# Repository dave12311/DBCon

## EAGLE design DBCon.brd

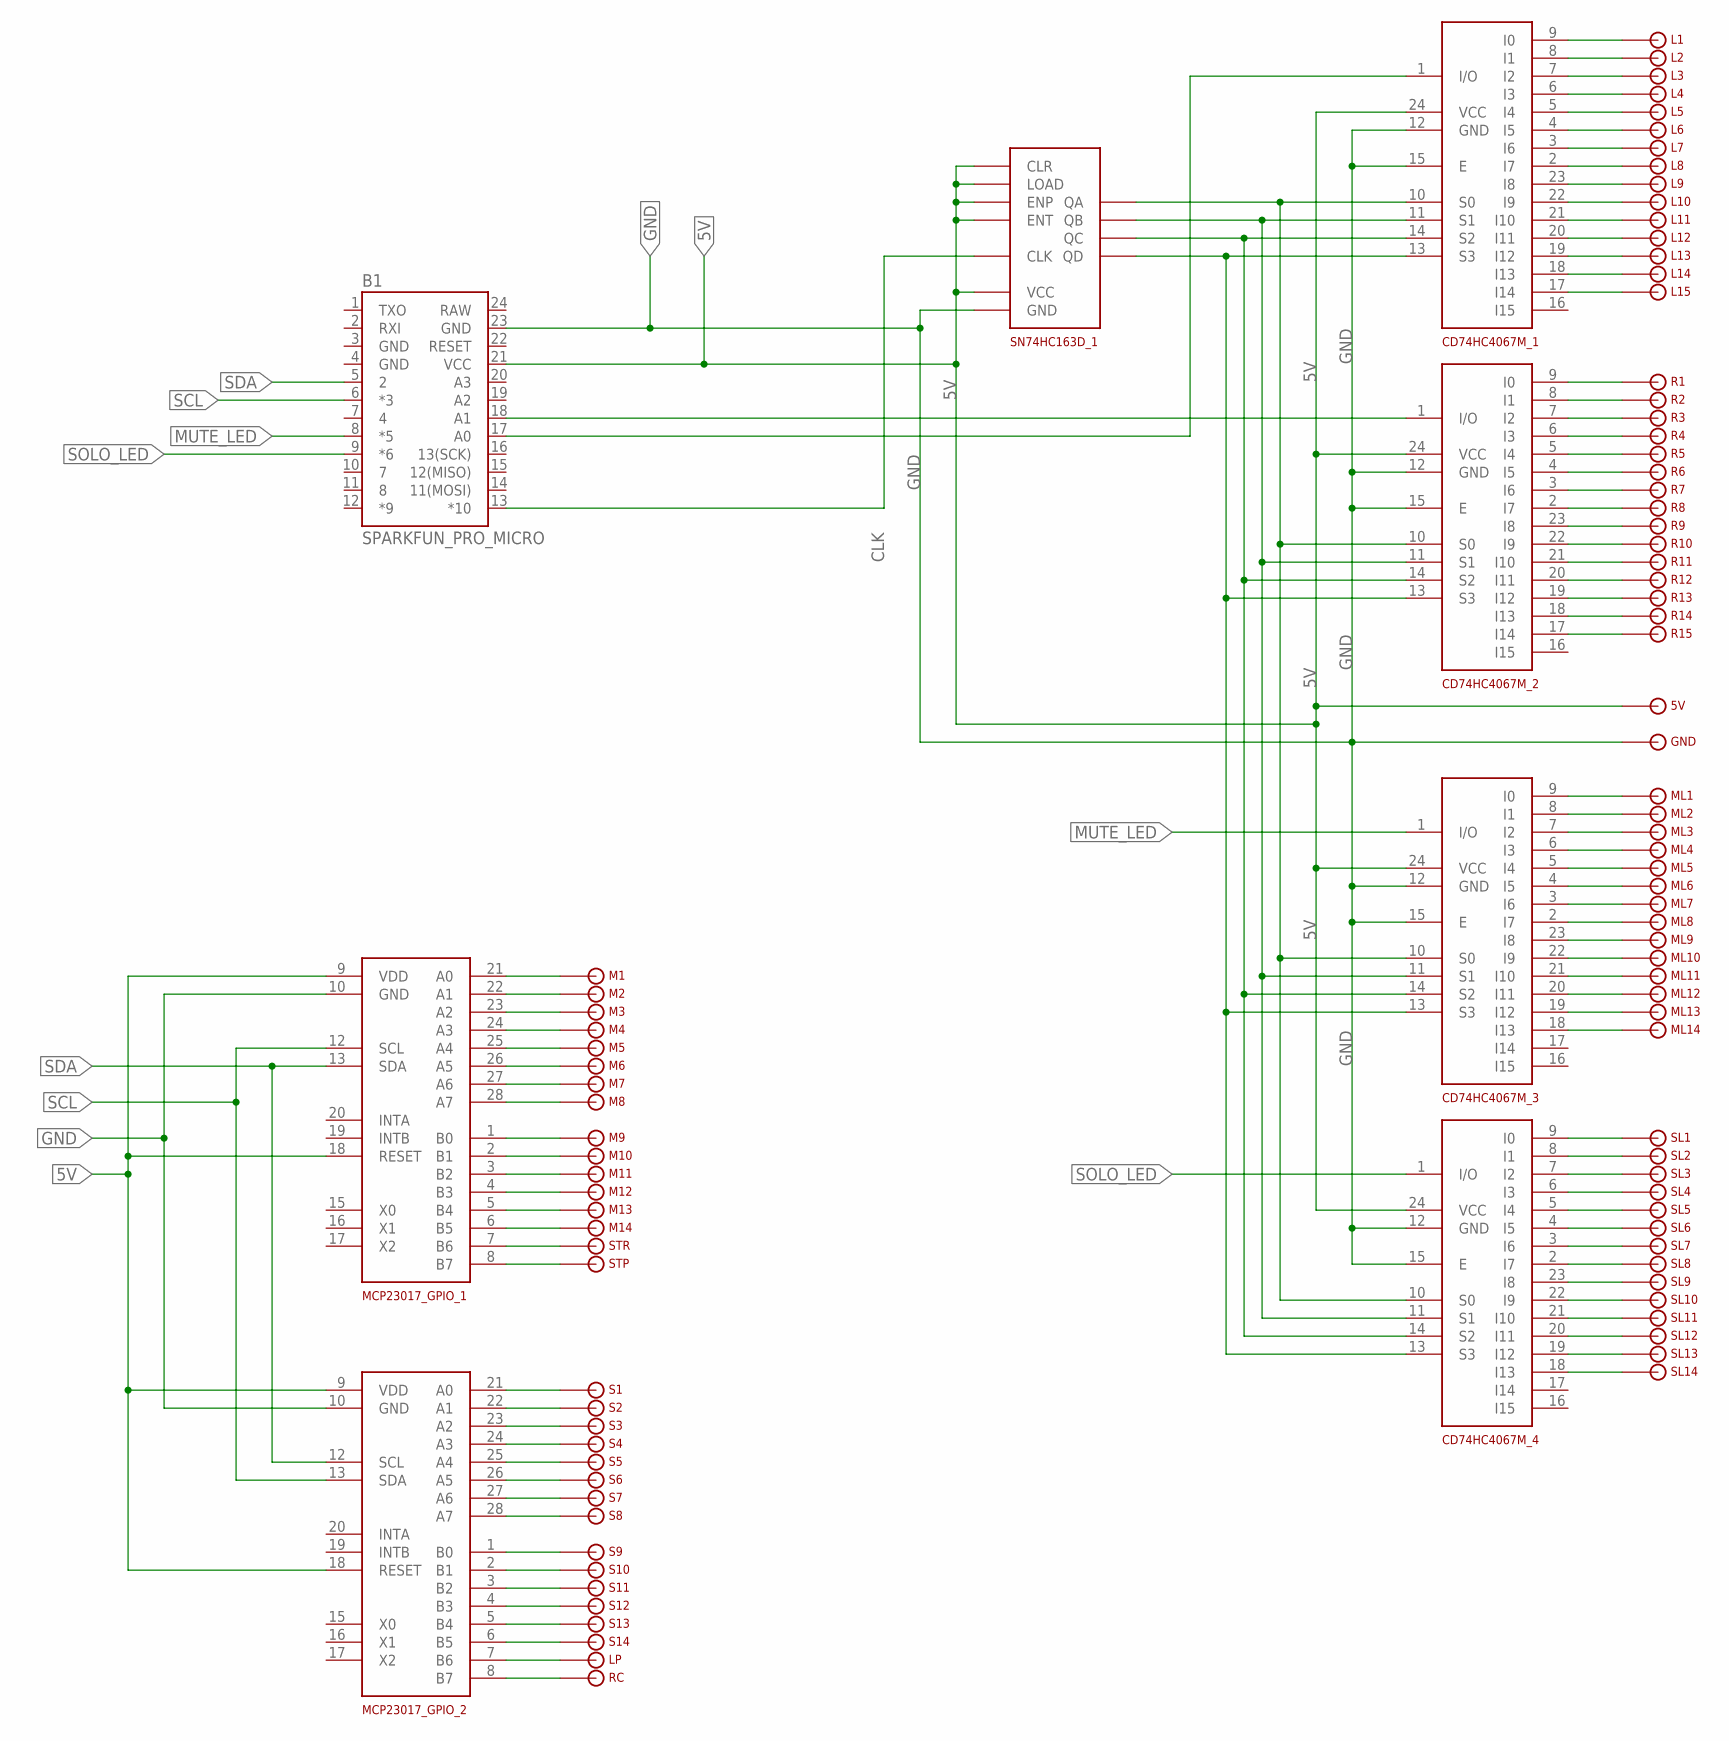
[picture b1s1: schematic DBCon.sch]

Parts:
5V: 1_PIN; CON1
B1: SPARKFUN_PRO_MICRO
CD74HC4067M_1, CD74HC4067M_2, CD74HC4067M_3, CD74HC4067M_4: CD74HC4067M_DEMUX; SO24
GND: 1_PIN; CON1
L1, L2, L3, L4, L5, L6, L7, L8, L9, L10, L11, L12, L13, L14, L15: 1_PIN; CON1
LP: 1_PIN; CON1
M1, M2, M3, M4, M5, M6, M7, M8, M9, M10, M11, M12, M13, M14: 1_PIN; CON1
MCP23017_GPIO_1, MCP23017_GPIO_2: MCP23017_GPIO; DIL28-3
ML1, ML2, ML3, ML4, ML5, ML6, ML7, ML8, ML9, ML10, ML11, ML12, ML13, ML14: 1_PIN; CON1
R1, R2, R3, R4, R5, R6, R7, R8, R9, R10, R11, R12, R13, R14, R15: 1_PIN; CON1
RC: 1_PIN; CON1
S1, S2, S3, S4, S5, S6, S7, S8, S9, S10, S11, S12, S13, S14: 1_PIN; CON1
SL1, SL2, SL3, SL4, SL5, SL6, SL7, SL8, SL9, SL10, SL11, SL12, SL13, SL14: 1_PIN; CON1
SN74HC163D_1: SN74HC163D_COUNTER; SO16
STP: 1_PIN; CON1
STR: 1_PIN; CON1

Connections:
5V: 5V.P$1, B1.21 (VCC), CD74HC4067M_1.24 (VCC), CD74HC4067M_2.24 (VCC), CD74HC4067M_3.24 (VCC), CD74HC4067M_4.24 (VCC), MCP23017_GPIO_1.9 (VDD), MCP23017_GPIO_1.18 (RESET), MCP23017_GPIO_2.9 (VDD), MCP23017_GPIO_2.18 (RESET), SN74HC163D_1.1 (CLR), SN74HC163D_1.7 (ENP), SN74HC163D_1.9 (LOAD), SN74HC163D_1.10 (ENT), SN74HC163D_1.16 (VCC)
A: CD74HC4067M_1.10 (S0), CD74HC4067M_2.10 (S0), CD74HC4067M_3.10 (S0), CD74HC4067M_4.10 (S0), SN74HC163D_1.14 (QA)
B: CD74HC4067M_1.11 (S1), CD74HC4067M_2.11 (S1), CD74HC4067M_3.11 (S1), CD74HC4067M_4.11 (S1), SN74HC163D_1.13 (QB)
C: CD74HC4067M_1.14 (S2), CD74HC4067M_2.14 (S2), CD74HC4067M_3.14 (S2), CD74HC4067M_4.14 (S2), SN74HC163D_1.12 (QC)
CLK: B1.13 (*10), SN74HC163D_1.2 (CLK)
D: CD74HC4067M_1.13 (S3), CD74HC4067M_2.13 (S3), CD74HC4067M_3.13 (S3), CD74HC4067M_4.13 (S3), SN74HC163D_1.11 (QD)
GND: B1.3 (GND), B1.4 (GND), B1.23 (GND), CD74HC4067M_1.12 (GND), CD74HC4067M_1.15 (E), CD74HC4067M_2.12 (GND), CD74HC4067M_2.15 (E), CD74HC4067M_3.12 (GND), CD74HC4067M_3.15 (E), CD74HC4067M_4.12 (GND), CD74HC4067M_4.15 (E), GND.P$1, MCP23017_GPIO_1.10 (GND), MCP23017_GPIO_2.10 (GND), SN74HC163D_1.8 (GND)
L_IO: B1.17 (A0), CD74HC4067M_1.1 (I/O)
MUTE_LED: B1.8 (*5), CD74HC4067M_3.1 (I/O)
unnamed: M1.P$1, MCP23017_GPIO_1.21 (A0)
unnamed: M2.P$1, MCP23017_GPIO_1.22 (A1)
unnamed: M3.P$1, MCP23017_GPIO_1.23 (A2)
unnamed: CD74HC4067M_3.9 (I0), ML1.P$1
unnamed: CD74HC4067M_3.8 (I1), ML2.P$1
unnamed: CD74HC4067M_3.7 (I2), ML3.P$1
unnamed: CD74HC4067M_3.6 (I3), ML4.P$1
unnamed: M4.P$1, MCP23017_GPIO_1.24 (A3)
unnamed: M5.P$1, MCP23017_GPIO_1.25 (A4)
unnamed: CD74HC4067M_1.9 (I0), L1.P$1
unnamed: CD74HC4067M_1.8 (I1), L2.P$1
unnamed: CD74HC4067M_1.7 (I2), L3.P$1
unnamed: CD74HC4067M_1.6 (I3), L4.P$1
unnamed: CD74HC4067M_1.5 (I4), L5.P$1
unnamed: CD74HC4067M_1.4 (I5), L6.P$1
unnamed: CD74HC4067M_1.3 (I6), L7.P$1
unnamed: CD74HC4067M_1.2 (I7), L8.P$1
unnamed: CD74HC4067M_1.23 (I8), L9.P$1
unnamed: CD74HC4067M_1.22 (I9), L10.P$1
unnamed: CD74HC4067M_1.21 (I10), L11.P$1
unnamed: CD74HC4067M_1.20 (I11), L12.P$1
unnamed: CD74HC4067M_1.19 (I12), L13.P$1
unnamed: CD74HC4067M_1.18 (I13), L14.P$1
unnamed: CD74HC4067M_1.17 (I14), L15.P$1
unnamed: CD74HC4067M_2.9 (I0), R1.P$1
unnamed: CD74HC4067M_2.8 (I1), R2.P$1
unnamed: CD74HC4067M_2.7 (I2), R3.P$1
unnamed: CD74HC4067M_2.6 (I3), R4.P$1
unnamed: CD74HC4067M_2.5 (I4), R5.P$1
unnamed: CD74HC4067M_2.4 (I5), R6.P$1
unnamed: CD74HC4067M_2.3 (I6), R7.P$1
unnamed: CD74HC4067M_2.2 (I7), R8.P$1
unnamed: CD74HC4067M_2.23 (I8), R9.P$1
unnamed: CD74HC4067M_2.22 (I9), R10.P$1
unnamed: CD74HC4067M_2.21 (I10), R11.P$1
unnamed: CD74HC4067M_2.20 (I11), R12.P$1
unnamed: CD74HC4067M_2.19 (I12), R13.P$1
unnamed: CD74HC4067M_2.18 (I13), R14.P$1
unnamed: CD74HC4067M_2.17 (I14), R15.P$1
unnamed: M6.P$1, MCP23017_GPIO_1.26 (A5)
unnamed: M7.P$1, MCP23017_GPIO_1.27 (A6)
unnamed: M8.P$1, MCP23017_GPIO_1.28 (A7)
unnamed: M9.P$1, MCP23017_GPIO_1.1 (B0)
unnamed: M10.P$1, MCP23017_GPIO_1.2 (B1)
unnamed: M11.P$1, MCP23017_GPIO_1.3 (B2)
unnamed: M12.P$1, MCP23017_GPIO_1.4 (B3)
unnamed: M13.P$1, MCP23017_GPIO_1.5 (B4)
unnamed: M14.P$1, MCP23017_GPIO_1.6 (B5)
unnamed: MCP23017_GPIO_1.7 (B6), STR.P$1
unnamed: MCP23017_GPIO_1.8 (B7), STP.P$1
unnamed: MCP23017_GPIO_2.21 (A0), S1.P$1
unnamed: MCP23017_GPIO_2.22 (A1), S2.P$1
unnamed: MCP23017_GPIO_2.23 (A2), S3.P$1
unnamed: MCP23017_GPIO_2.24 (A3), S4.P$1
unnamed: MCP23017_GPIO_2.25 (A4), S5.P$1
unnamed: MCP23017_GPIO_2.26 (A5), S6.P$1
unnamed: MCP23017_GPIO_2.27 (A6), S7.P$1
unnamed: MCP23017_GPIO_2.28 (A7), S8.P$1
unnamed: MCP23017_GPIO_2.1 (B0), S9.P$1
unnamed: MCP23017_GPIO_2.2 (B1), S10.P$1
unnamed: MCP23017_GPIO_2.3 (B2), S11.P$1
unnamed: MCP23017_GPIO_2.4 (B3), S12.P$1
unnamed: MCP23017_GPIO_2.5 (B4), S13.P$1
unnamed: MCP23017_GPIO_2.6 (B5), S14.P$1
unnamed: LP.P$1, MCP23017_GPIO_2.7 (B6)
unnamed: MCP23017_GPIO_2.8 (B7), RC.P$1
unnamed: CD74HC4067M_3.5 (I4), ML5.P$1
unnamed: CD74HC4067M_3.4 (I5), ML6.P$1
unnamed: CD74HC4067M_3.3 (I6), ML7.P$1
unnamed: CD74HC4067M_3.2 (I7), ML8.P$1
unnamed: CD74HC4067M_3.23 (I8), ML9.P$1
unnamed: CD74HC4067M_3.22 (I9), ML10.P$1
unnamed: CD74HC4067M_3.21 (I10), ML11.P$1
unnamed: CD74HC4067M_3.20 (I11), ML12.P$1
unnamed: CD74HC4067M_3.19 (I12), ML13.P$1
unnamed: CD74HC4067M_3.18 (I13), ML14.P$1
unnamed: CD74HC4067M_4.9 (I0), SL1.P$1
unnamed: CD74HC4067M_4.8 (I1), SL2.P$1
unnamed: CD74HC4067M_4.7 (I2), SL3.P$1
unnamed: CD74HC4067M_4.6 (I3), SL4.P$1
unnamed: CD74HC4067M_4.5 (I4), SL5.P$1
unnamed: CD74HC4067M_4.4 (I5), SL6.P$1
unnamed: CD74HC4067M_4.3 (I6), SL7.P$1
unnamed: CD74HC4067M_4.2 (I7), SL8.P$1
unnamed: CD74HC4067M_4.23 (I8), SL9.P$1
unnamed: CD74HC4067M_4.22 (I9), SL10.P$1
unnamed: CD74HC4067M_4.21 (I10), SL11.P$1
unnamed: CD74HC4067M_4.20 (I11), SL12.P$1
unnamed: CD74HC4067M_4.19 (I12), SL13.P$1
unnamed: CD74HC4067M_4.18 (I13), SL14.P$1
RAW: B1.24 (RAW)
R_IO: B1.18 (A1), CD74HC4067M_2.1 (I/O)
SCL: B1.6 (*3), MCP23017_GPIO_1.12 (SCL), MCP23017_GPIO_2.13 (SDA)
SDA: B1.5 (2), MCP23017_GPIO_1.13 (SDA), MCP23017_GPIO_2.12 (SCL)
SOLO_LED: B1.9 (*6), CD74HC4067M_4.1 (I/O)

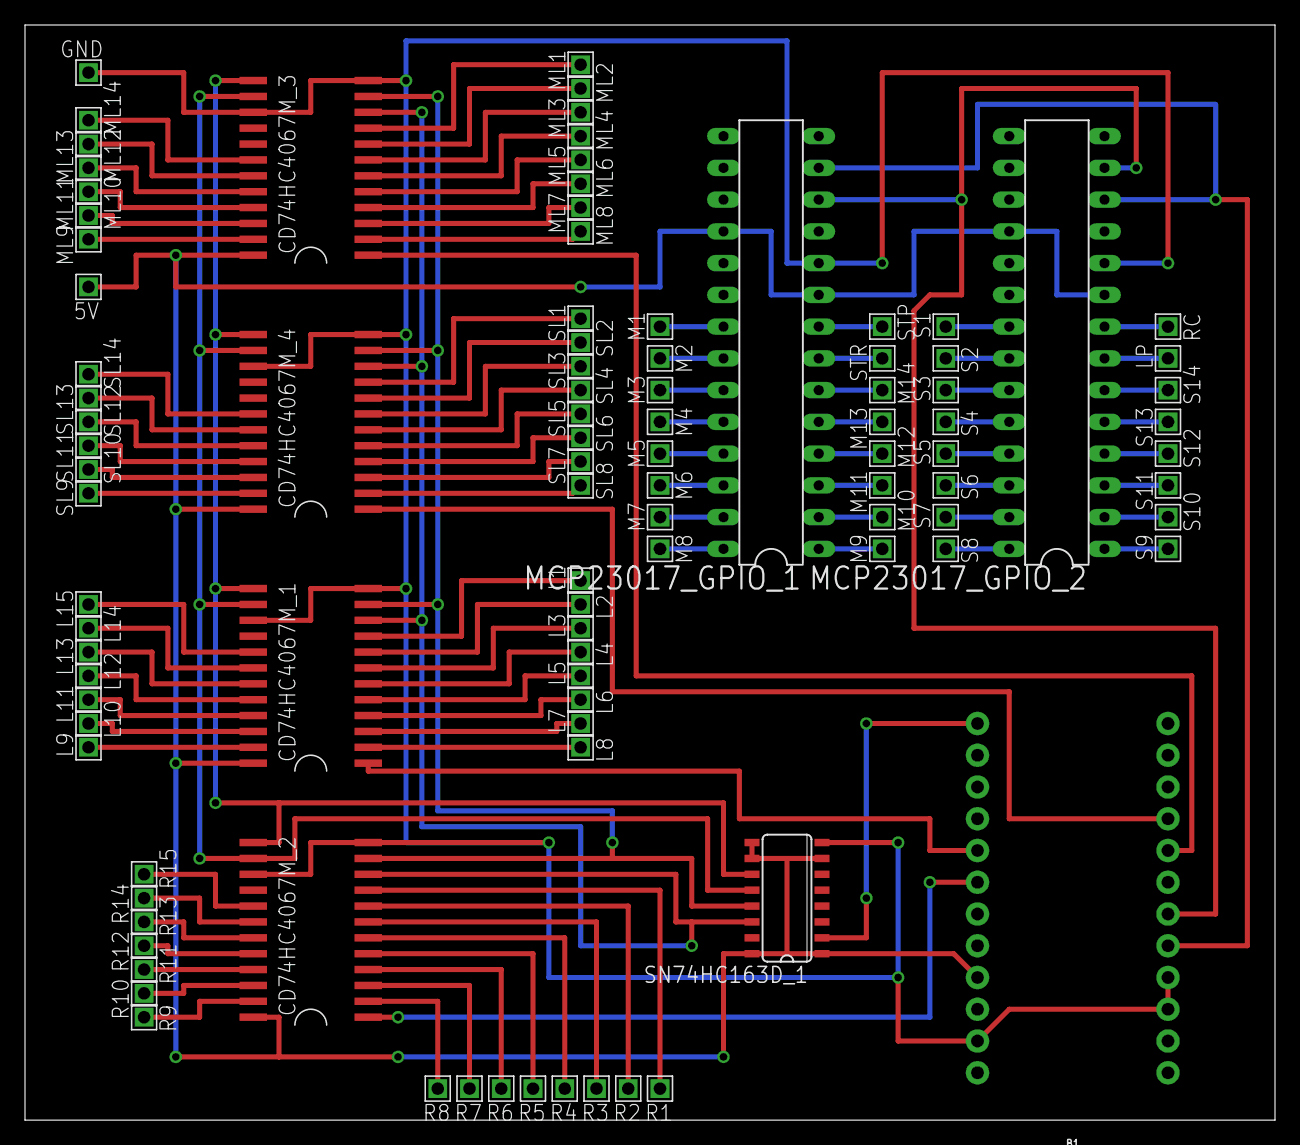
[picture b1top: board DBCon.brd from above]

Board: 2 copper layers, 100.0 x 87.6 mm, 100 parts (0 on the bottom side), 103 nets.

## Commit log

2017-04-24 New version (final?)
2017-04-24 New version fix
2017-04-25 Freed up analog pin
2017-05-20 something changed
2017-12-12 Added library for IO expander
